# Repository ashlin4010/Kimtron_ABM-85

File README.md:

# Kimtron ABM-85 #

This repository contains some notes and incomplete schematics for the Kimtron ABM-85 terminal.

I own two Kimtron ABM-85 terminals both of witch have faults, in this repository I share the notes I and others have made while trying to get them working.

ROM images can be found at [bitsavers.org](https://bitsavers.org/pdf/kimtron/Kimtron_ABM-85/advertisement/) and in the repo.

## Notes ##

* Memory is not required for the screen to initialize
* UART is not required for the screen to initialize
* Edge connector can be unscrewed can passed out the front for easy testing
* DO NOT solder to the board while plugged in but off, caps hold a charge and sort to the iron
* Keyboard will be beep regardless of the logic board functioning at all
* The CRT will not display anything if there is no video signal.

### System 1 - Fresh out of storage, worked for 30min then failed ###
* CRT chip 8275 had died
* U15 74LS08 had an internal short between inputs
* CRT was working then failed when board failed, likely connected

### System 2 - Fresh out of storage, system did not work at all ###
* CRT chip 8275 had died
* Character ROM damaged
* 8085 dead
* One UART dead
* Some/all RAM dead
* 8155 dead, pin 7 stuck a 3v
* CRT is working but unstable

### System 3 - Failed Parts ###
* All 2114
* 8275 U8
* 74LS163 U14

### System 4 - Failed Parts ###
* All 2114
* MC1400 x2
* MC1489
* 8275 U8
* 8155 U33
* 74LS163 U14
* 74LS175 U11
* 74LS08 U11

### Observation and Thoughts ###
Originally when I tested both of these terminals both had good power supplies, and good CRTs but only on of the logic boards worked. Both CRTs were unstable, the image had a tendency to lose sink and scroll. The terminal with a good logic board I left running for about 15-30 minutes, when I came back to it the screen had gone blank. Doing some testing the logic board had died, so had the CRT.

Both U15 (74LS08) and the 8275 had died, as well as the CRT. I suspect that some component in the CRT driver board has failed and killed both boards. As the CRT was functioning previously I'm inclined to believe a capacitor develop a short. My next steps will be to recap both CRT drive board and repair any damage.

## Replacement Capacitors ##

https://docs.google.com/spreadsheets/d/1czg9hMJ3bNXz6wbedZvZkCWXic-MMVokBJp4r8-iu80/edit?usp=sharing

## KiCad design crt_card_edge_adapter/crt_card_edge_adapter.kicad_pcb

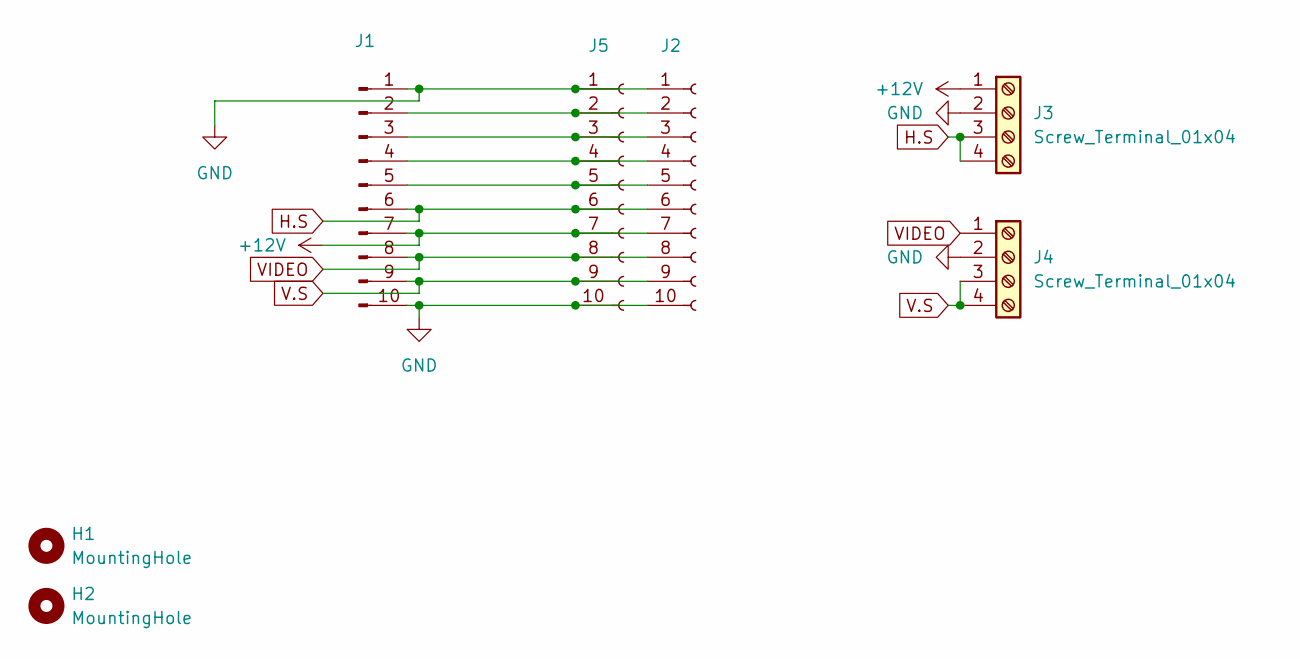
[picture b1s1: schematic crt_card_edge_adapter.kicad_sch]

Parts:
H1, H2: MountingHole; MountingHole_2.2mm_M2
J1: Conn_01x10_Pin; CRT_P0.156_10P
J2, J5: Conn_01x10_Socket; PinHeader_1x10_P2.54mm_Vertical
J3, J4: Screw_Terminal_01x04; TerminalBlock_bornier-4_P5.08mm

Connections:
+12V: J1.7, J2.7, J3.1, J5.7
GND: J1.1, J1.10, J2.1, J2.10, J3.2, J4.2, J5.1, J5.10
H.S: J1.6, J2.6, J3.3, J3.4, J5.6
unnamed: J1.2, J2.2, J5.2
unnamed: J1.3, J2.3, J5.3
unnamed: J1.4, J2.4, J5.4
unnamed: J1.5, J2.5, J5.5
V.S: J1.9, J2.9, J4.3, J4.4, J5.9
VIDEO: J1.8, J2.8, J4.1, J5.8

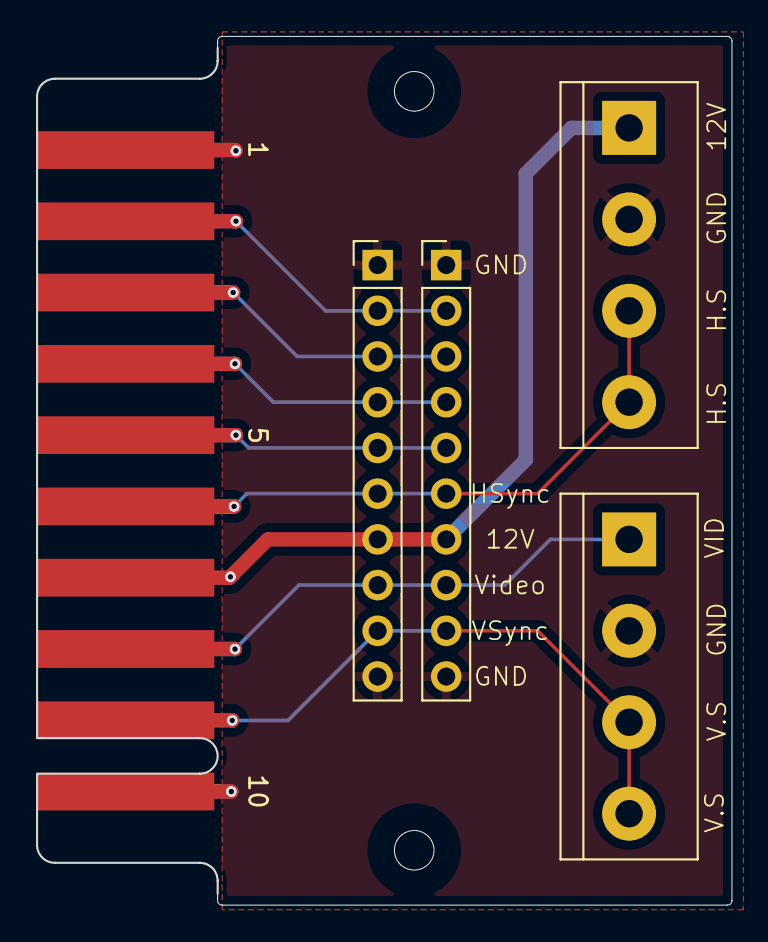
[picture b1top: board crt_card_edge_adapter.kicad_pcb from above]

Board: 2 copper layers, 38.6 x 48.2 mm, 7 parts (0 on the bottom side), 9 nets.

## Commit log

2023-12-31 init commit
2024-01-03 replacment caps
2024-07-05 Added crt_card_edge_adapter board
2025-02-05 Added new schematics and two new systems to the list
